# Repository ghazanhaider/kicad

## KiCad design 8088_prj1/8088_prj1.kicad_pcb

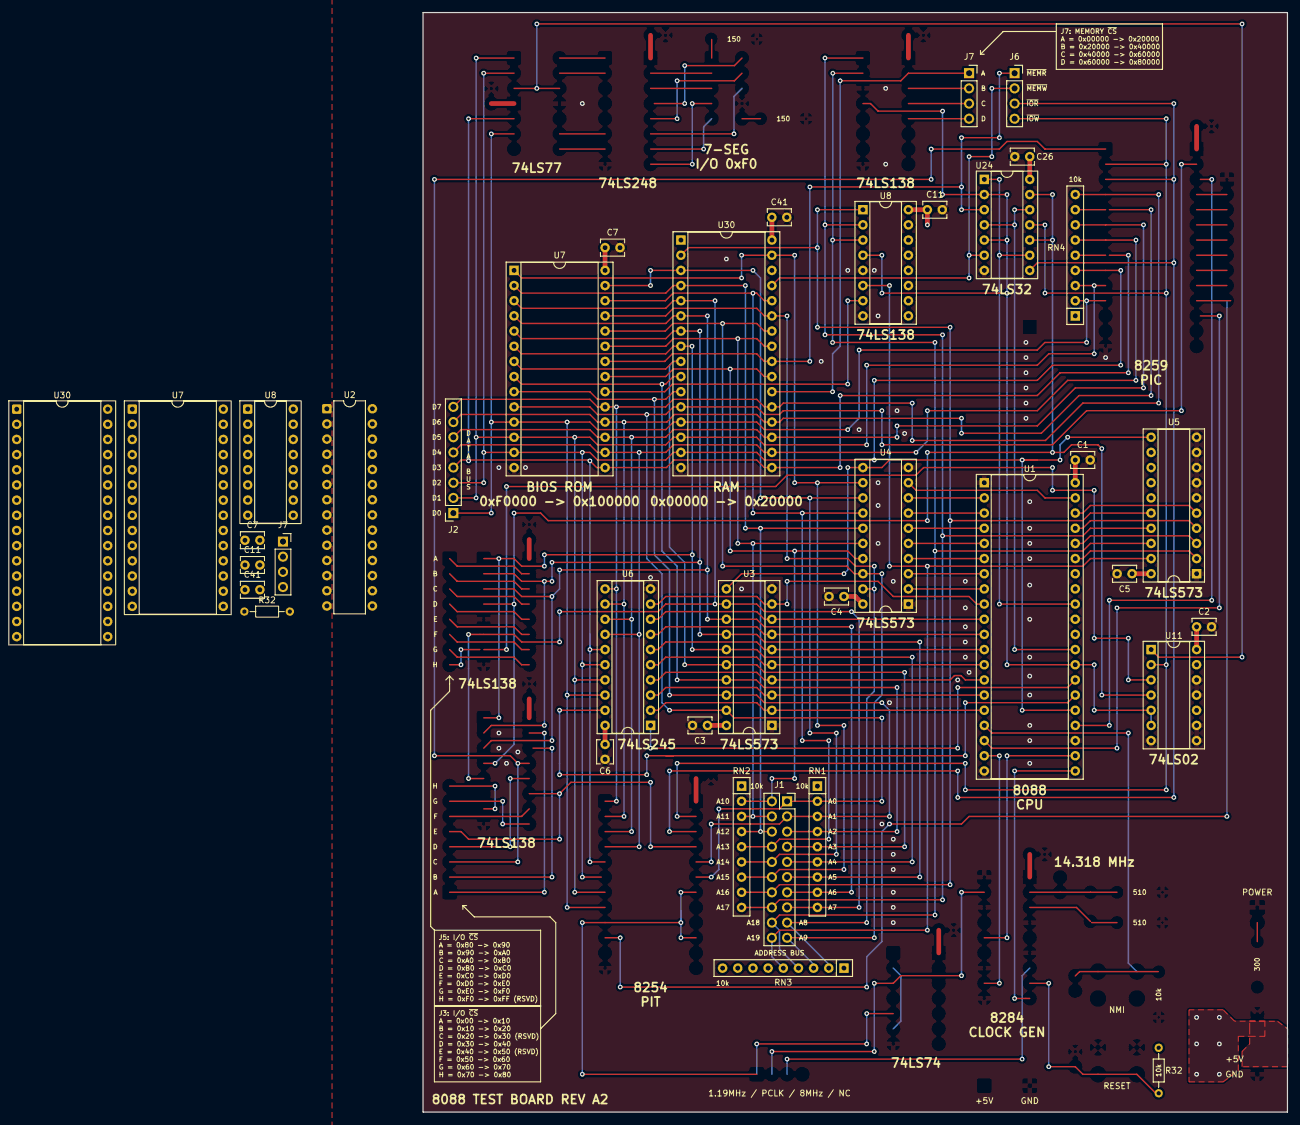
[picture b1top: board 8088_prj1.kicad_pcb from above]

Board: 4 copper layers, 144.8 x 184.1 mm, 38 parts (0 on the bottom side), 70 nets.

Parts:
C1, C2, C3, C4, C5, C6, C7, C7#2, C11, C11#2, C26, C41, C41#2: 0.1uF 20% Ceramic; C_Disc_D3.8mm_W2.6mm_P2.50mm
J1: Conn_02x10_Counter_Clockwise; PinSocket_2x10_P2.54mm_Vertical
J2: Conn_01x08; PinSocket_1x08_P2.54mm_Vertical
J6, J7, J7#2: Conn_01x04; PinSocket_1x04_P2.54mm_Vertical
R32, R32#2: 10k; R_Axial_DIN0204_L3.6mm_D1.6mm_P7.62mm_Horizontal
RN1, RN2, RN3, RN4: R_Network08; R_Array_SIP9
U1: 8088; DIP-40_W15.24mm_Socket
U2: ATmega328P-P; DIP-28_W7.62mm
U3, U4, U5: 74LS573; DIP-20_W7.62mm_Socket
U6: 74HC245; DIP-20_W7.62mm_Socket
U7: AT29F010B; DIP-28_W15.24mm_Socket
U7#2: W27C512 BIOS ROM; DIP-28_W15.24mm_Socket
U8, U8#2: 74LS138; DIP-16_W7.62mm_Socket
U11: 74LS02; DIP-14_W7.62mm_Socket
U24: 74LS32; DIP-14_W7.62mm_Socket
U30, U30#2: AS6C1008-55PCN; DIP-32_W15.24mm_Socket

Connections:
+5V: C1.1, C2.1, C3.1, C4.1, C5.1, C6.1, C7.1, C7#2.1, C11.1, C11#2.1, C26.1, C41.1, C41#2.1, R32.1, R32#2.1, RN1.1 (common), RN2.1 (common), RN3.1 (common), RN4.1 (common), U1.22 (READY), U1.33 (MN/~MX), U1.40 (VCC), U2.7 (VCC), U2.20 (AVCC), U3.20 (VCC), U4.20 (VCC), U5.20 (VCC), U6.20 (VCC), U7#2.28 (VCC), U8.6 (E3), U8.16 (VCC), U8#2.16 (VCC), U11.14 (VCC), U24.14 (VCC), U30.30 (CS2), U30.32 (VCC), U30#2.30 (CS2), U30#2.32 (VCC)
/8088_A8: U1.8 (A8), U4.2 (D0)
/8088_A9: U1.7 (A9), U4.3 (D1)
/8088_A10: U1.6 (A10), U4.4 (D2)
/8088_A11: U1.5 (A11), U4.5 (D3)
/8088_A12: U1.4 (A12), U4.6 (D4)
/8088_A13: U1.3 (A13), U4.7 (D5)
/8088_A14: U1.2 (A14), U4.8 (D6)
/8088_A15: U1.39 (A15), U4.9 (D7)
/8088_A16: U1.38 (A16/S3), U5.5 (D3)
/8088_A17: U1.37 (A17/S4), U5.4 (D2)
/8088_A18: U1.36 (A18/S5), U5.3 (D1)
/8088_A19: U1.35 (A19/S6), U5.2 (D0)
/8088_AD0: U1.16 (AD0), U3.2 (D0), U6.2 (A0)
/8088_AD1: U1.15 (AD1), U3.3 (D1), U6.3 (A1)
/8088_AD2: U1.14 (AD2), U3.4 (D2), U6.4 (A2)
/8088_AD3: U1.13 (AD3), U3.5 (D3), U6.5 (A3)
/8088_AD4: U1.12 (AD4), U3.6 (D4), U6.6 (A4)
/8088_AD5: U1.11 (AD5), U3.7 (D5), U6.7 (A5)
/8088_AD6: U1.10 (AD6), U3.8 (D6), U6.8 (A6)
/8088_AD7: U1.9 (AD7), U3.9 (D7), U6.9 (A7)
/8088_ALE: U1.25 (ALE), U3.11 (Load), U4.11 (Load), U5.11 (Load)
/8088_CLK: U1.19 (CLK), U2.15 (PB1)
/8088_DEN#: U1.26 (DEN), U6.19 (CE)
/8088_DT/R#: U1.27 (DT/~R), U6.1 (A->B)
/8088_IO/M#: U1.28 (IO/~M), U8.5 (E2), U8#2.4 (E1), U11.5, U11.6, U24.2, U24.5
/8088_RD#: U1.32 (~RD), U24.1, U24.9
/8088_RESET: R32#2.2, U1.21 (RESET), U2.10 (XTAL2/PB7)
/8088_WR#: U1.29 (WR), U24.4, U24.12
/A0: J1.1, RN1.2 (R1), U3.19 (Q0), U7.12 (A0), U7#2.10 (A0), U30.12 (A0), U30#2.12 (A0)
/A1: J1.3, RN1.3 (R2), U3.18 (Q1), U7.11 (A1), U7#2.9 (A1), U30.11 (A1), U30#2.11 (A1)
/A2: J1.5, RN1.4 (R3), U3.17 (Q2), U7.10 (A2), U7#2.8 (A2), U30.10 (A2), U30#2.10 (A2)
/A3: J1.7, RN1.5 (R4), U3.16 (Q3), U7.9 (A3), U7#2.7 (A3), U30.9 (A3), U30#2.9 (A3)
/A4: J1.9, RN1.6 (R5), U3.15 (Q4), U7.8 (A4), U7#2.6 (A4), U30.8 (A4), U30#2.8 (A4)
/A5: J1.11, RN1.7 (R6), U3.14 (Q5), U7.7 (A5), U7#2.5 (A5), U30.7 (A5), U30#2.7 (A5)
/A6: J1.13, RN1.8 (R7), U3.13 (Q6), U7.6 (A6), U7#2.4 (A6), U30.6 (A6), U30#2.6 (A6)
/A7: J1.15, RN1.9 (R8), U3.12 (Q7), U7.5 (A7), U7#2.3 (A7), U30.5 (A7), U30#2.5 (A7)
/A8: J1.17, RN3.2 (R1), U4.19 (Q0), U7.27 (A8), U7#2.25 (A8), U30.27 (A8), U30#2.27 (A8)
/A9: J1.19, RN3.3 (R2), U4.18 (Q1), U7.26 (A9), U7#2.24 (A9), U30.26 (A9), U30#2.26 (A9)
/A10: J1.2, RN2.2 (R1), U4.17 (Q2), U7.23 (A10), U7#2.21 (A10), U30.23 (A10), U30#2.23 (A10)
/A11: J1.4, RN2.3 (R2), U4.16 (Q3), U7.25 (A11), U7#2.23 (A11), U30.25 (A11), U30#2.25 (A11)
/A12: J1.6, RN2.4 (R3), U4.15 (Q4), U7.4 (A12), U7#2.2 (A12), U30.4 (A12), U30#2.4 (A12)
/A13: J1.8, RN2.5 (R4), U4.14 (Q5), U7.28 (A13), U7#2.26 (A13), U30.28 (A13), U30#2.28 (A13)
/A14: J1.10, RN2.6 (R5), U4.13 (Q6), U7#2.27 (A14), U30.3 (A14), U30#2.3 (A14)
/A15: J1.12, RN2.7 (R6), U4.12 (Q7), U7.3 (A15), U7#2.1 (A15), U30.31 (A15)
/A16: J1.14, RN2.8 (R7), U5.16 (Q3), U7.2 (A16), U8#2.1 (A0), U30.2 (A16)
/A17: J1.16, RN2.9 (R8), U5.17 (Q2), U8.1 (A0), U8#2.2 (A1)
/A18: J1.18, RN3.4 (R3), U5.18 (Q1), U8.2 (A1), U8#2.3 (A2)
/A19: J1.20, RN3.5 (R4), U5.19 (Q0), U8.3 (A2), U8#2.6 (E3)
/BIOS_ROM_CS#: U7.22 (CE), U7#2.20 (CE#), U8.7 (O7), U8#2.7 (O7)
/D0: J2.1, RN4.2 (R1), U6.18 (B0), U7.13 (D0), U7#2.11 (Q0), U30.13 (Q0), U30#2.13 (Q0)
/D1: J2.2, RN4.3 (R2), U6.17 (B1), U7.14 (D1), U7#2.12 (Q1), U30.14 (Q1), U30#2.14 (Q1)
/D2: J2.3, RN4.4 (R3), U6.16 (B2), U7.15 (D2), U7#2.13 (Q2), U30.15 (Q2), U30#2.15 (Q2)
/D3: J2.4, RN4.5 (R4), U6.15 (B3), U7.17 (D3), U7#2.15 (Q3), U30.17 (Q3), U30#2.17 (Q3)
/D4: J2.5, RN4.6 (R5), U6.14 (B4), U7.18 (D4), U7#2.16 (Q4), U30.18 (Q4), U30#2.18 (Q4)
/D5: J2.6, RN4.7 (R6), U6.13 (B5), U7.19 (D5), U7#2.17 (Q5), U30.19 (Q5), U30#2.19 (Q5)
/D6: J2.7, RN4.8 (R7), U6.12 (B6), U7.20 (D6), U7#2.18 (Q6), U30.20 (Q6), U30#2.20 (Q6)
/D7: J2.8, RN4.9 (R8), U6.11 (B7), U7.21 (D7), U7#2.19 (Q7), U30.21 (Q7), U30#2.21 (Q7)
/RAM/~RAM_A_CS: J7.1, U30.22 (~CS1)
/RAM_CS#: U8.15 (O0), U30#2.22 (~CS1)
/~IOR: J6.3, U24.8
/~IOW: J6.4, U24.11
/~MEMR: J6.1, U7.24 (OE), U7#2.22 (OE#), U24.3, U30.24 (~OE), U30#2.24 (~OE)
/~MEMW: J6.2, U24.6, U30.29 (~WE), U30#2.29 (~WE)
GND: C1.2, C2.2, C3.2, C4.2, C5.2, C6.2, C7.2, C7#2.2, C11.2, C11#2.2, C26.2, C41.2, C41#2.2, U1.1 (GND), U1.17 (NMI), U1.18 (INTR), U1.20 (GND), U1.23 (~TEST), U1.31 (HOLD), U2.8 (GND), U2.22 (GND), U3.1 (OE), U3.10 (GND), U4.1 (OE), U4.10 (GND), U5.1 (OE), U5.6 (D4), U5.7 (D5), U5.8 (D6), U5.9 (D7), U5.10 (GND), U6.10 (GND), U7.16 (GND), U7#2.14 (GND), U8.4 (E1), U8.8 (GND), U8#2.5 (E2), U8#2.8 (GND), U11.2, U11.3, U11.7 (GND), U11.8, U11.9, U11.11, U11.12, U24.7 (GND), U30.16 (GND), U30#2.16 (GND)
unnamed: J7#2.1, U8.14 (O1)
unnamed: J7.2, J7#2.2, U8.13 (O2)
unnamed: J7.3, J7#2.3, U8.12 (O3)
unnamed: J7.4, J7#2.4, U8.11 (O4)
unnamed: U11.4, U24.10, U24.13

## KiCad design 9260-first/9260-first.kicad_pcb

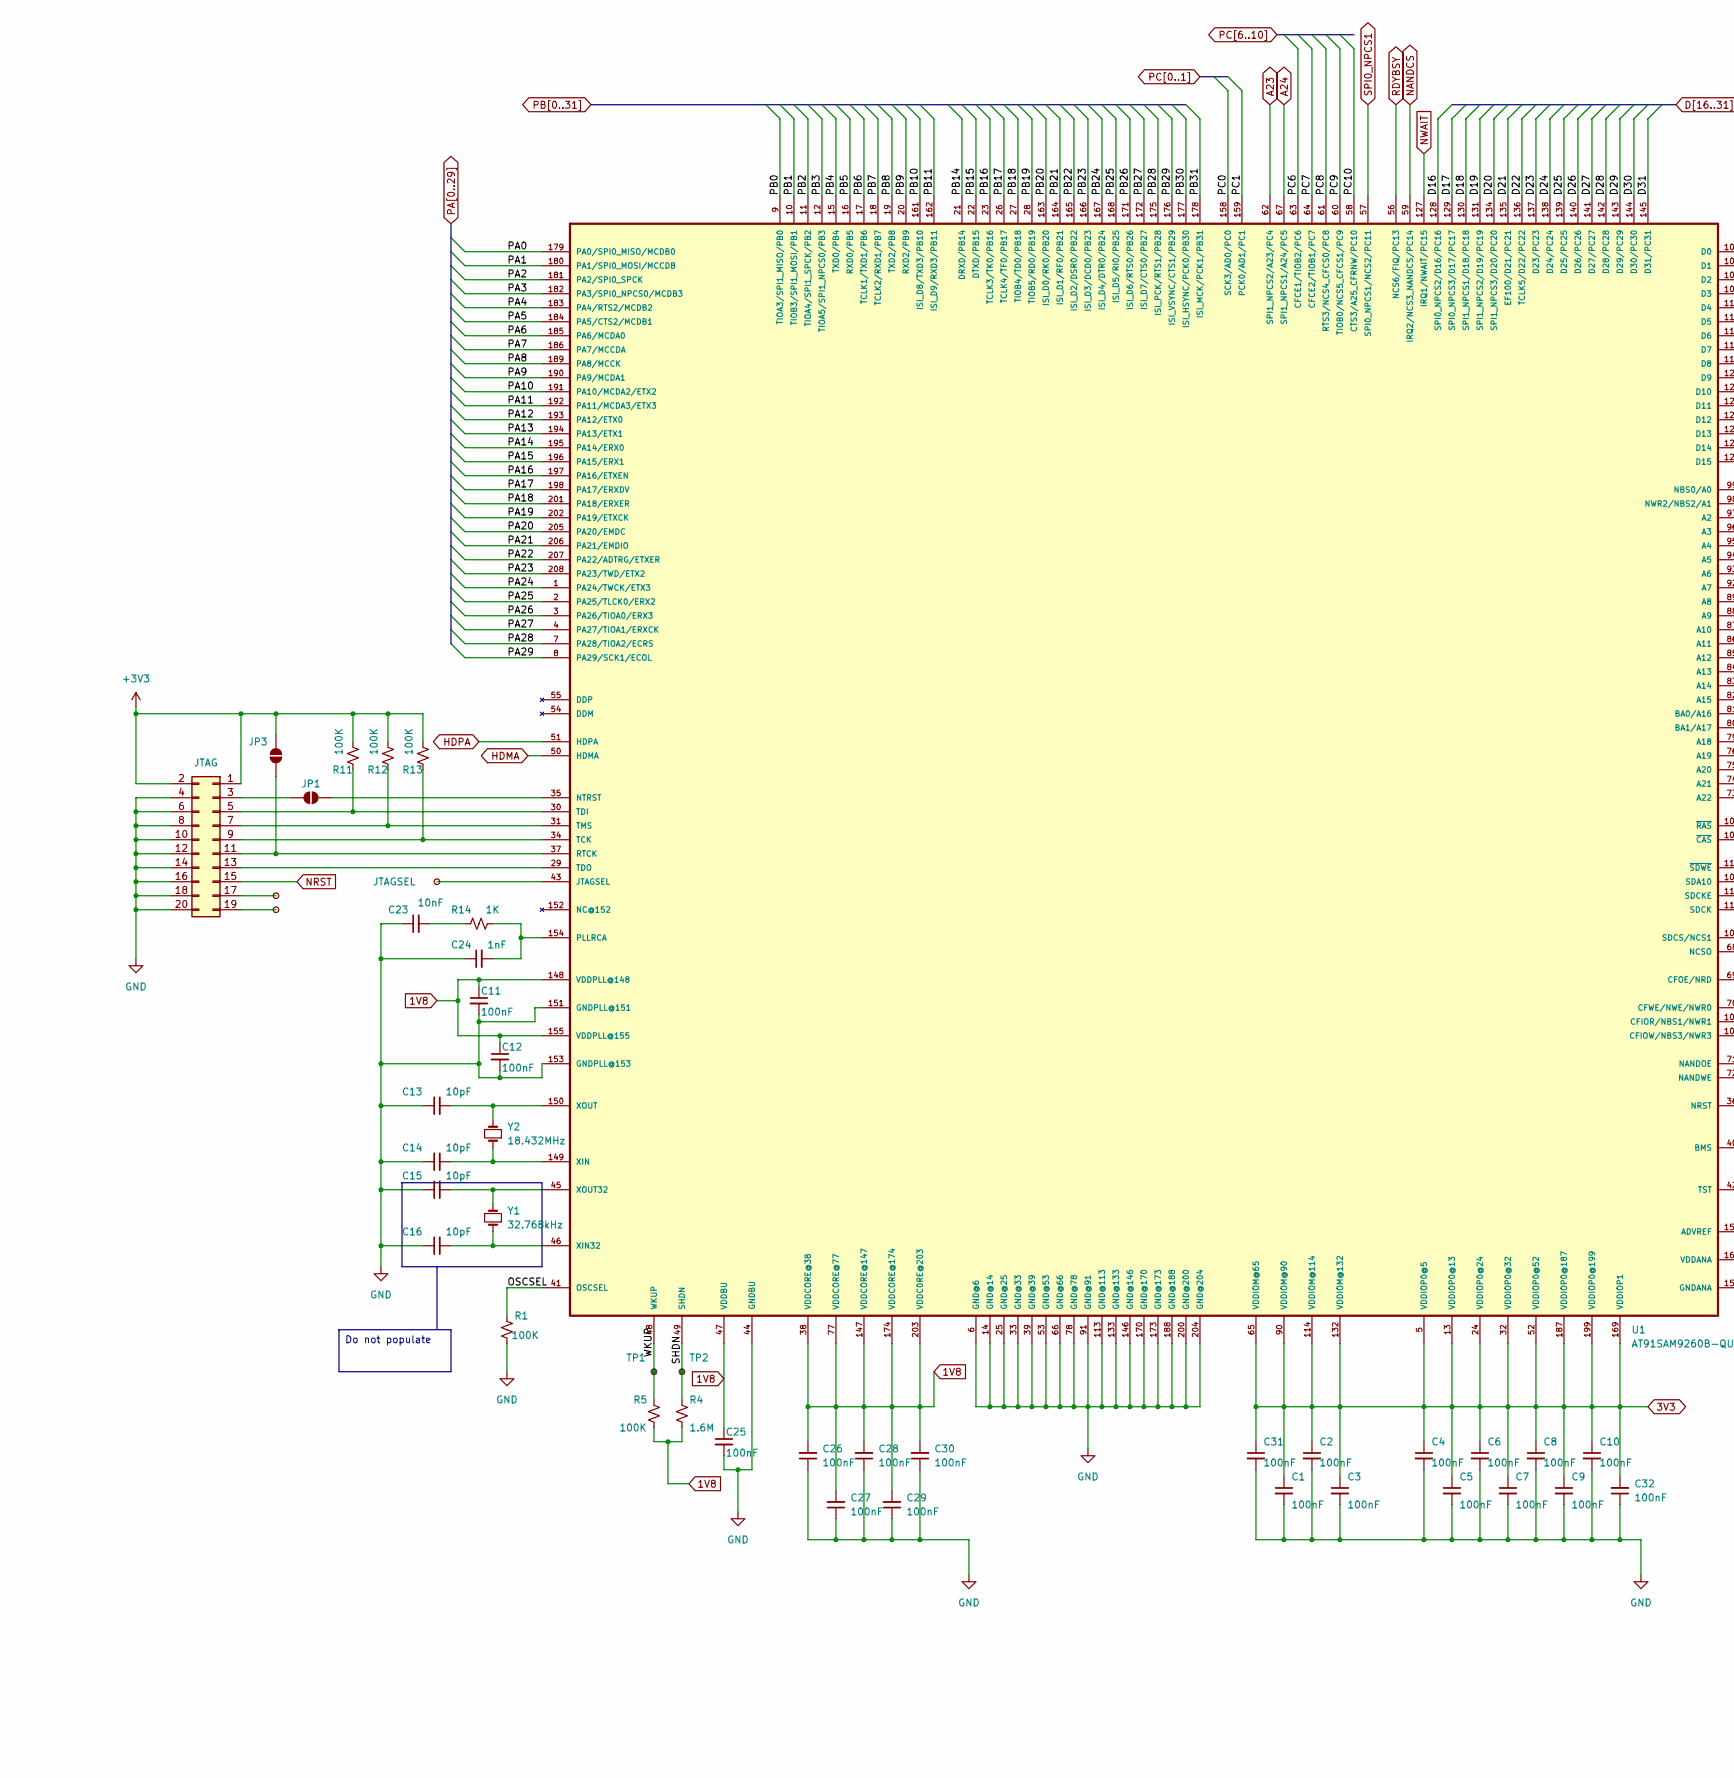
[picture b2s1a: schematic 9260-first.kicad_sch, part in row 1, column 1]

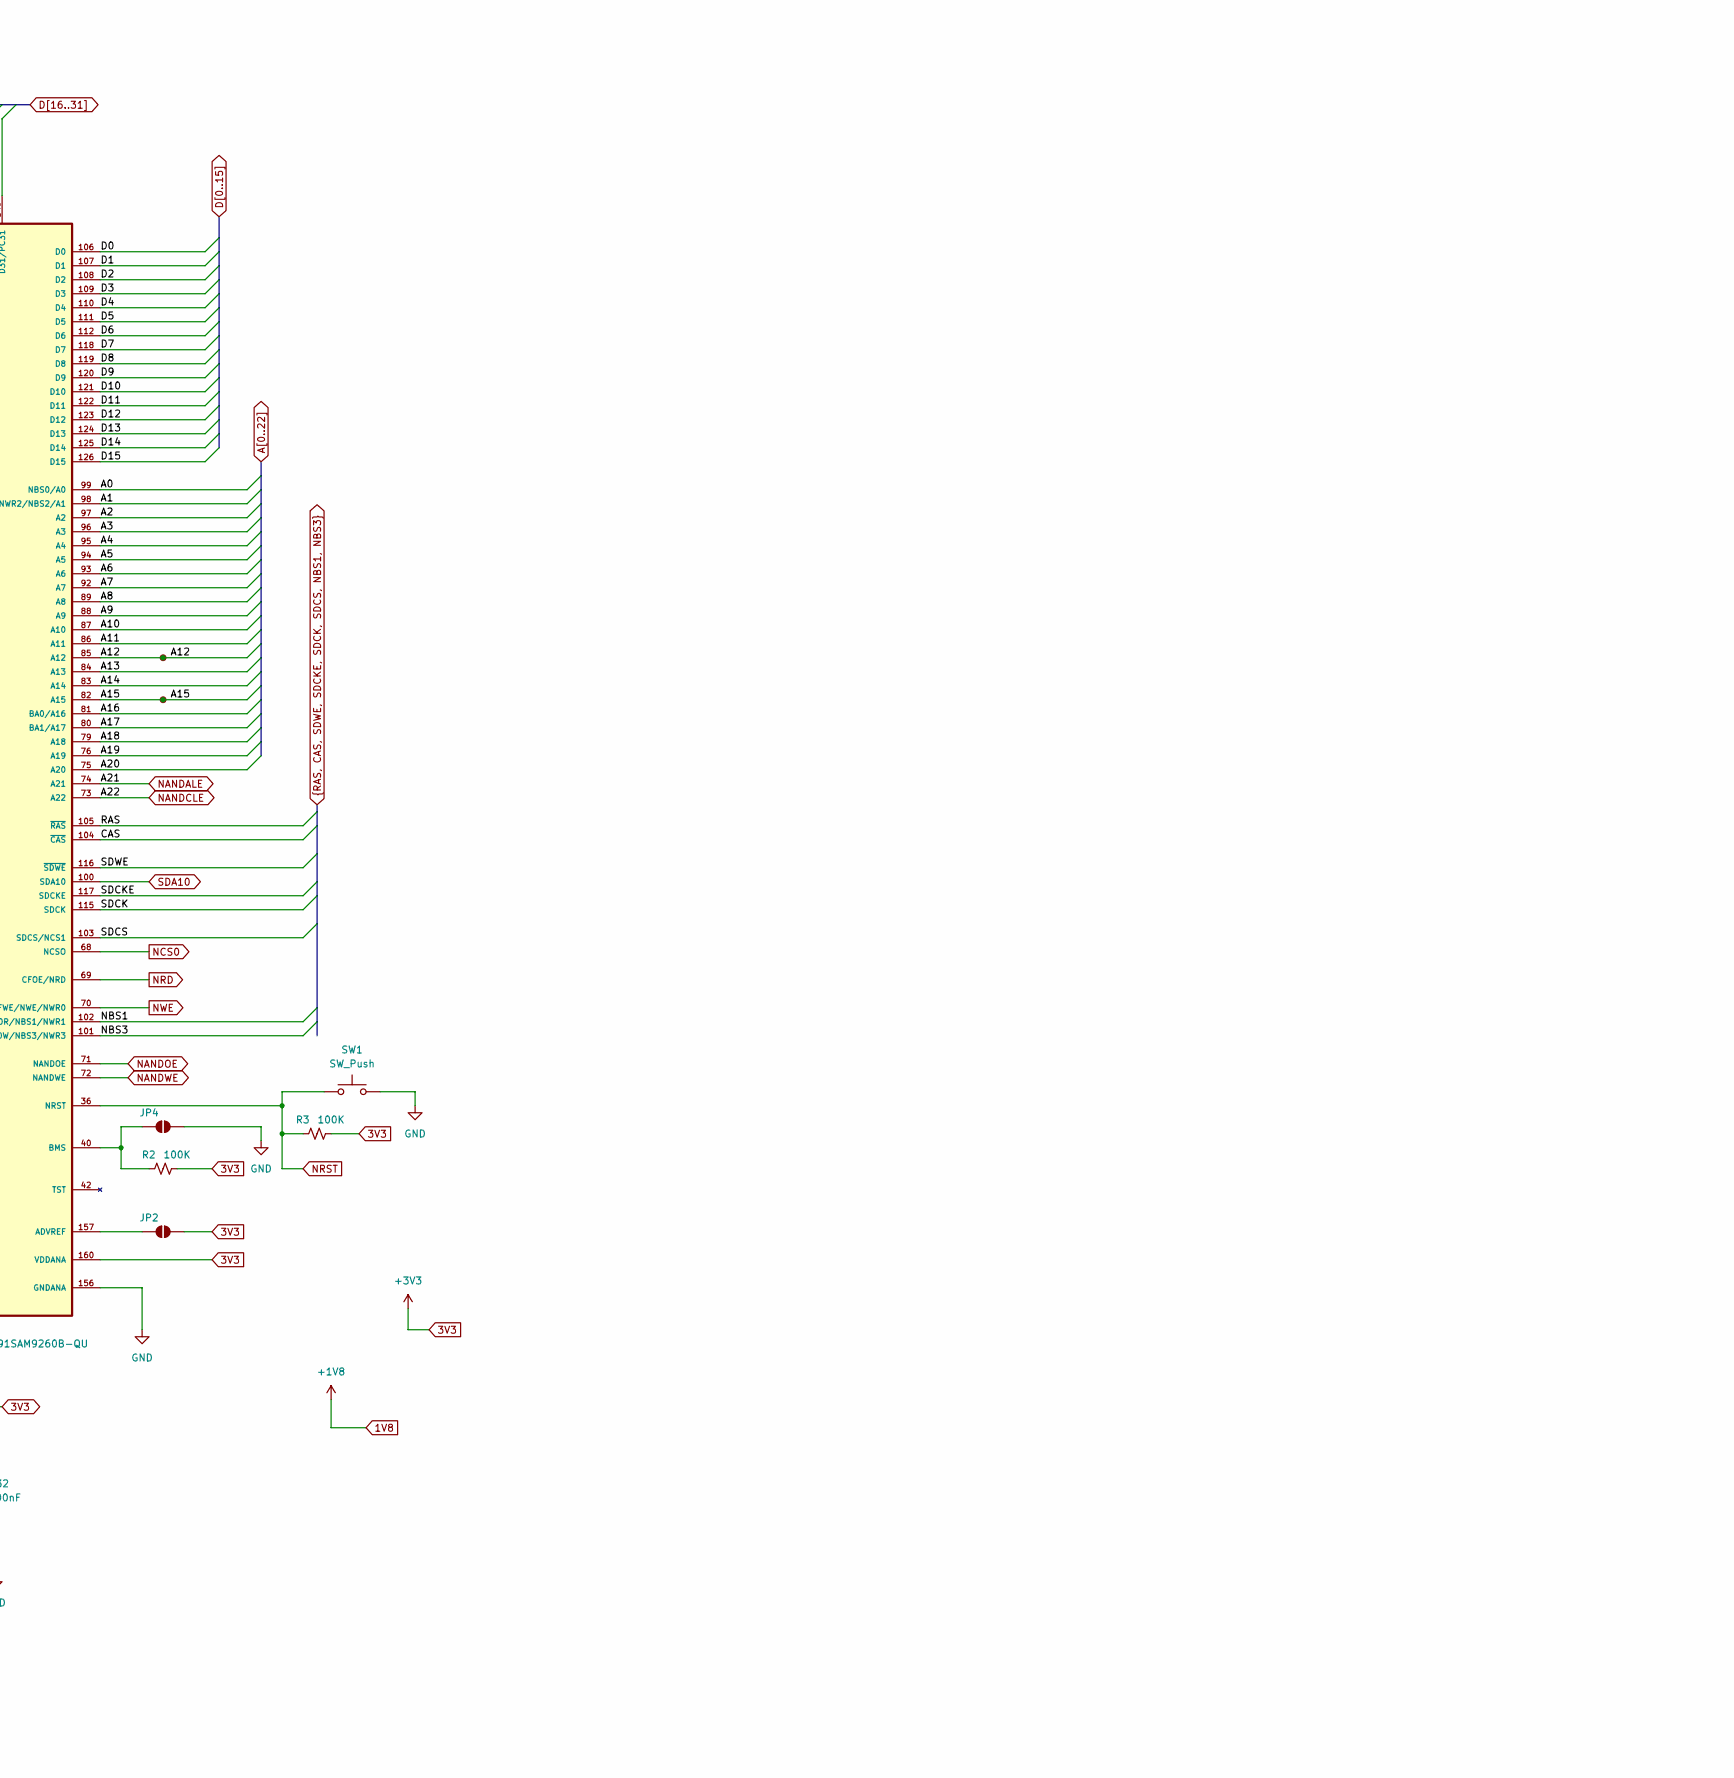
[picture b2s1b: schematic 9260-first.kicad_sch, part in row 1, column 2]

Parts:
C1, C2, C3, C4, C5, C6, C7, C8, C9, C10, C11, C12, C25, C26, C27, C28, C29, C30, C31, C32: 100nF; C_0805_2012Metric
C13, C14, C15, C16: 10pF; C_0805_2012Metric
C23: 10nF; C_0805_2012Metric
C24: 1nF; C_0805_2012Metric
J1: JTAG; PinHeader_2x10_P2.54mm_Vertical
JP1, JP2, JP3, JP4: SolderJumper_2_Open; SolderJumper-2_P1.3mm_Open_Pad1.0x1.5mm
R1, R2, R3, R5, R11, R12, R13: 100K; R_0805_2012Metric
R4: 1.6M; R_0805_2012Metric
R14: 1K; R_0805_2012Metric
SW1: SW_Push; SW_Push_1P1T_NO_6x6mm_H9.5mm
TP1, TP2: TestPoint_Small; TestPoint_Plated_Hole_D2.0mm
TP3, TP5, TP7: A12; TestPoint_Plated_Hole_D2.0mm
TP4: A15; TestPoint_Plated_Hole_D2.0mm
TP6: JTAGSEL; TestPoint_Plated_Hole_D2.0mm
U1: AT91SAM9260B-QU; PQFP208
Y1: 32.768kHz; Crystal_SMD_HC49-SD
Y2: 18.432MHz; Crystal_SMD_HC49-SD

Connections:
1V8: C11.1, C12.1, C25.1, C26.2, C27.2, C28.2, C29.2, C30.2, R4.2, R5.2, U1.38 (VDDCORE@38), U1.47 (VDDBU), U1.77 (VDDCORE@77), U1.147 (VDDCORE@147), U1.148 (VDDPLL@148), U1.155 (VDDPLL@155), U1.174 (VDDCORE@174), U1.203 (VDDC0RE@203); also elsewhere on the board
3V3: C1.1, C2.1, C3.1, C4.1, C5.1, C6.1, C7.1, C8.1, C9.1, C10.1, C31.1, C32.2, J1.1, J1.2, JP2.2 (B), JP3.2 (B), R2.2, R3.2, R11.1, R12.1, R13.1, U1.5 (VDDIOP0@5), U1.13 (VDDIOP0@13), U1.24 (VDDIOP0@24), U1.32 (VDDIOP0@32), U1.52 (VDDIOP0@52), U1.65 (VDDIOM@65), U1.90 (VDDIOM@90), U1.114 (VDDIOM@114), U1.132 (VDDIOM@132), U1.160 (VDDANA), U1.169 (VDDIOP1), U1.187 (VDDIOP0@187), U1.199 (VDDIOP0@199); also elsewhere on the board
/OSCSEL: R1.1, U1.41 (OSCSEL)
/SHDN: R4.1, TP2.1, U1.49 (SHDN)
/WKUP: R5.1, TP1.1, U1.48 (WKUP)
A0: U1.99 (NBS0/A0); also elsewhere on the board
A1: U1.98 (NWR2/NBS2/A1); also elsewhere on the board
A2: U1.97 (A2); also elsewhere on the board
A3: U1.96 (A3); also elsewhere on the board
A4: U1.95 (A4); also elsewhere on the board
A5: U1.94 (A5); also elsewhere on the board
A6: U1.93 (A6); also elsewhere on the board
A7: U1.92 (A7); also elsewhere on the board
A8: U1.89 (A8); also elsewhere on the board
A9: U1.88 (A9); also elsewhere on the board
A10: U1.87 (A10); also elsewhere on the board
A11: U1.86 (A11); also elsewhere on the board
A12: TP3.1, U1.85 (A12)
A13: U1.84 (A13); also elsewhere on the board
A14: U1.83 (A14); also elsewhere on the board
A15: TP4.1, U1.82 (A15)
A16: U1.81 (BA0/A16); also elsewhere on the board
A17: U1.80 (BA1/A17); also elsewhere on the board
A18: U1.79 (A18)
A19: U1.76 (A19)
A20: U1.75 (A20)
A23: U1.62 (SPI1_NPCS2/A23/PC4)
A24: U1.67 (SPI1_NPCS1/A24/PC5)
CAS: U1.104 (~CAS); also elsewhere on the board
D0: U1.106 (D0); also elsewhere on the board
D1: U1.107 (D1); also elsewhere on the board
D2: U1.108 (D2); also elsewhere on the board
D3: U1.109 (D3); also elsewhere on the board
D4: U1.110 (D4); also elsewhere on the board
D5: U1.111 (D5); also elsewhere on the board
D6: U1.112 (D6); also elsewhere on the board
D7: U1.118 (D7); also elsewhere on the board
D8: U1.119 (D8); also elsewhere on the board
D9: U1.120 (D9); also elsewhere on the board
D10: U1.121 (D10); also elsewhere on the board
D11: U1.122 (D11); also elsewhere on the board
D12: U1.123 (D12); also elsewhere on the board
D13: U1.124 (D13); also elsewhere on the board
D14: U1.125 (D14); also elsewhere on the board
D15: U1.126 (D15); also elsewhere on the board
D16: U1.128 (SPI0_NPCS2/D16/PC16); also elsewhere on the board
D17: U1.129 (SPI0_NPCS3/D17/PC17); also elsewhere on the board
D18: U1.130 (SPI1_NPCS1/D18/PC18); also elsewhere on the board
D19: U1.131 (SPI1_NPCS2/D19/PC19); also elsewhere on the board
D20: U1.134 (SPI1_NPCS3/D20/PC20); also elsewhere on the board
D21: U1.135 (EF100/D21/PC21); also elsewhere on the board
D22: U1.136 (TCLK5/D22/PC22); also elsewhere on the board
D23: U1.137 (D23/PC23); also elsewhere on the board
D24: U1.138 (D24/PC24); also elsewhere on the board
D25: U1.139 (D25/PC25); also elsewhere on the board
D26: U1.140 (D26/PC26); also elsewhere on the board
D27: U1.141 (D27/PC27); also elsewhere on the board
D28: U1.142 (D28/PC28); also elsewhere on the board
D29: U1.143 (D29/PC29); also elsewhere on the board
D30: U1.144 (D30/PC30); also elsewhere on the board
D31: U1.145 (D31/PC31); also elsewhere on the board
GND: C1.2, C2.2, C3.2, C4.2, C5.2, C6.2, C7.2, C8.2, C9.2, C10.2, C11.2, C12.2, C13.1, C14.1, C15.1, C16.1, C23.1, C24.1, C25.2, C26.1, C27.1, C28.1, C29.1, C30.1, C31.2, C32.1, J1.4, J1.6, J1.8, J1.10, J1.12, J1.14, J1.16, J1.18, J1.20, JP4.2 (B), R1.2, SW1.2, U1.6 (GND@6), U1.14 (GND@14), U1.25 (GND@25), U1.33 (GND@33), U1.39 (GND@39), U1.44 (GNDBU), U1.53 (GND@53), U1.66 (GND@66), U1.78 (GND@78), U1.91 (GND@91), U1.113 (GND@113), U1.133 (GND@133), U1.146 (GND@146), U1.151 (GNDPLL@151), U1.153 (GNDPLL@153), U1.156 (GNDANA), U1.170 (GND@170), U1.173 (GND@173), U1.188 (GND@188), U1.200 (GND@200), U1.204 (GND@204); also elsewhere on the board
HDMA: U1.50 (HDMA); also elsewhere on the board
HDPA: U1.51 (HDPA); also elsewhere on the board
NANDALE: U1.74 (A21)
NANDCLE: U1.73 (A22)
NANDCS: U1.59 (IRQ2/NCS3_NANDCS/PC14)
NANDOE: U1.71 (NANDOE)
NANDWE: U1.72 (NANDWE)
NBS1: U1.102 (CFIOR/NBS1/NWR1); also elsewhere on the board
NBS3: U1.101 (CFIOW/NBS3/NWR3); also elsewhere on the board
NCS0: U1.68 (NCSO)
NRD: U1.69 (CFOE/NRD)
NRST: J1.15, R3.1, SW1.1, U1.36 (NRST); also elsewhere on the board
NWAIT: U1.127 (IRQ1/NWAIT/PC15)
NWE: U1.70 (CFWE/NWE/NWR0)
unnamed: C23.2, R14.1
unnamed: J1.3, JP1.1 (A)
unnamed: J1.5, R11.2, U1.30 (TDI)
unnamed: J1.7, R12.2, U1.31 (TMS)
unnamed: J1.9, R13.2, U1.34 (TCK)
unnamed: J1.11, JP3.1 (A), U1.37 (RTCK)
unnamed: J1.13, U1.29 (TDO)
unnamed: J1.17, TP5.1
unnamed: J1.19, TP7.1
unnamed: JP1.2 (B), U1.35 (NTRST)
unnamed: JP2.1 (A), U1.157 (ADVREF)
unnamed: JP4.1 (A), R2.1, U1.40 (BMS)
unnamed: TP6.1, U1.43 (JTAGSEL)
unnamed: C24.2, R14.2, U1.154 (PLLRCA)
unnamed: C16.2, U1.46 (XIN32), Y1.1
unnamed: C14.2, U1.149 (XIN), Y2.1
unnamed: C15.2, U1.45 (XOUT32), Y1.2
unnamed: C13.2, U1.150 (XOUT), Y2.2
PA0: U1.179 (PA0/SPI0_MISO/MCDB0); also elsewhere on the board
PA1: U1.180 (PA1/SPI0_MOSI/MCCDB); also elsewhere on the board
PA2: U1.181 (PA2/SPI0_SPCK); also elsewhere on the board
PA3: U1.182 (PA3/SPI0_NPCS0/MCDB3); also elsewhere on the board
PA4: U1.183 (PA4/RTS2/MCDB2); also elsewhere on the board
PA5: U1.184 (PA5/CTS2/MCDB1); also elsewhere on the board
PA6: U1.185 (PA6/MCDA0); also elsewhere on the board
PA7: U1.186 (PA7/MCCDA); also elsewhere on the board
PA8: U1.189 (PA8/MCCK); also elsewhere on the board
PA9: U1.190 (PA9/MCDA1); also elsewhere on the board
PA10: U1.191 (PA10/MCDA2/ETX2); also elsewhere on the board
PA11: U1.192 (PA11/MCDA3/ETX3); also elsewhere on the board
PA12: U1.193 (PA12/ETX0); also elsewhere on the board
PA13: U1.194 (PA13/ETX1); also elsewhere on the board
PA14: U1.195 (PA14/ERX0); also elsewhere on the board
PA15: U1.196 (PA15/ERX1); also elsewhere on the board
PA16: U1.197 (PA16/ETXEN); also elsewhere on the board
PA17: U1.198 (PA17/ERXDV); also elsewhere on the board
PA18: U1.201 (PA18/ERXER); also elsewhere on the board
PA19: U1.202 (PA19/ETXCK); also elsewhere on the board
PA20: U1.205 (PA20/EMDC); also elsewhere on the board
PA21: U1.206 (PA21/EMDIO); also elsewhere on the board
PA22: U1.207 (PA22/ADTRG/ETXER); also elsewhere on the board
PA23: U1.208 (PA23/TWD/ETX2); also elsewhere on the board
PA24: U1.1 (PA24/TWCK/ETX3); also elsewhere on the board
PA25: U1.2 (PA25/TLCK0/ERX2); also elsewhere on the board
PA26: U1.3 (PA26/TIOA0/ERX3); also elsewhere on the board
PA27: U1.4 (PA27/TIOA1/ERXCK); also elsewhere on the board
PA28: U1.7 (PA28/TIOA2/ECRS); also elsewhere on the board
PA29: U1.8 (PA29/SCK1/ECOL); also elsewhere on the board
PB0: U1.9 (TIOA3/SPI1_MISO/PB0)
PB1: U1.10 (TIOB3/SPI1_MOSI/PB1)
PB2: U1.11 (TIOA4/SPI1_SPCK/PB2)
PB3: U1.12 (TIOA5/SPI1_NPCS0/PB3)
PB4: U1.15 (TXD0/PB4)
PB5: U1.16 (RXD0/PB5)
PB6: U1.17 (TCLK1/TXD1/PB6)
PB7: U1.18 (TCLK2/RXD1/PB7)
PB8: U1.19 (TXD2/PB8)
PB9: U1.20 (RXD2/PB9)
PB10: U1.161 (ISI_D8/TXD3/PB10); also elsewhere on the board
PB11: U1.162 (ISI_D9/RXD3/PB11); also elsewhere on the board
PB14: U1.21 (DRXD/PB14); also elsewhere on the board
PB15: U1.22 (DTXD/PB15); also elsewhere on the board
PB16: U1.23 (TCLK3/TK0/PB16)
PB17: U1.26 (TCLK4/TF0/PB17)
PB18: U1.27 (TIOB4/TD0/PB18)
PB19: U1.28 (TIOB5/RD0/PB19)
PB20: U1.163 (ISI_D0/RK0/PB20); also elsewhere on the board
PB21: U1.164 (ISI_D1/RF0/PB21); also elsewhere on the board
PB22: U1.165 (ISI_D2/DSR0/PB22); also elsewhere on the board
PB23: U1.166 (ISI_D3/DCD0/PB23); also elsewhere on the board
PB24: U1.167 (ISI_D4/DTR0/PB24); also elsewhere on the board
PB25: U1.168 (ISI_D5/RI0/PB25); also elsewhere on the board
PB26: U1.171 (ISI_D6/RTS0/PB26); also elsewhere on the board
PB27: U1.172 (ISI_D7/CTS0/PB27); also elsewhere on the board
PB28: U1.175 (ISI_PCK/RTS1/PB28); also elsewhere on the board
PB29: U1.176 (ISI_VSYNC/CTS1/PB29); also elsewhere on the board
PB30: U1.177 (ISI_HSYNC/PCK0/PB30); also elsewhere on the board
PB31: U1.178 (ISI_MCK/PCK1/PB31); also elsewhere on the board
PC0: U1.158 (SCK3/AD0/PC0); also elsewhere on the board
PC1: U1.159 (PCK0/AD1/PC1); also elsewhere on the board
PC6: U1.63 (CFCE1/TIOB2/PC6)
PC7: U1.64 (CFCE2/TIOB1/PC7)
PC8: U1.61 (RTS3/NCS4_CFCS0/PC8)
PC9: U1.60 (TIOB0/NCS5_CFCS1/PC9)
PC10: U1.58 (CTS3/A25_CFRNW/PC10)
RAS: U1.105 (~RAS); also elsewhere on the board
RDYBSY: U1.56 (NCS6/FIQ/PC13)
SDA10: U1.100 (SDA10); also elsewhere on the board
SDCK: U1.115 (SDCK); also elsewhere on the board
SDCKE: U1.117 (SDCKE); also elsewhere on the board
SDCS: U1.103 (SDCS/NCS1); also elsewhere on the board
SDWE: U1.116 (~SDWE); also elsewhere on the board
SPI0_NPCS1: U1.57 (SPI0_NPCS1/NCS2/PC11); also elsewhere on the board

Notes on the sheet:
Do not populate

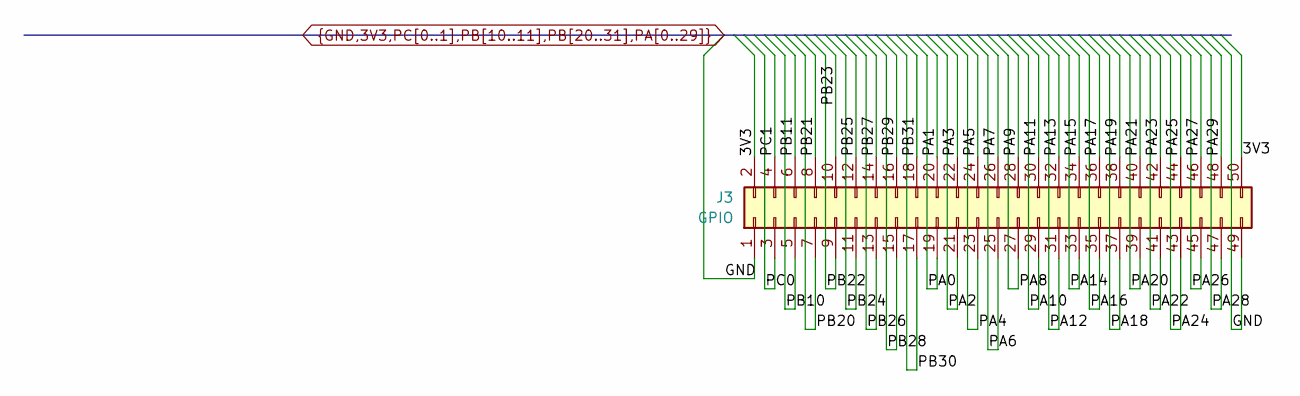
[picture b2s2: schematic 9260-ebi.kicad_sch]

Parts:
J3: GPIO; PinHeader_2x25_P2.54mm_Vertical

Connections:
3V3: J3.2, J3.50; also elsewhere on the board
GND: J3.1, J3.49; also elsewhere on the board
PA0: J3.19; also elsewhere on the board
PA1: J3.20; also elsewhere on the board
PA2: J3.21; also elsewhere on the board
PA3: J3.22; also elsewhere on the board
PA4: J3.23; also elsewhere on the board
PA5: J3.24; also elsewhere on the board
PA6: J3.25; also elsewhere on the board
PA7: J3.26; also elsewhere on the board
PA8: J3.27; also elsewhere on the board
PA9: J3.28; also elsewhere on the board
PA10: J3.29; also elsewhere on the board
PA11: J3.30; also elsewhere on the board
PA12: J3.31; also elsewhere on the board
PA13: J3.32; also elsewhere on the board
PA14: J3.33; also elsewhere on the board
PA15: J3.34; also elsewhere on the board
PA16: J3.35; also elsewhere on the board
PA17: J3.36; also elsewhere on the board
PA18: J3.37; also elsewhere on the board
PA19: J3.38; also elsewhere on the board
PA20: J3.39; also elsewhere on the board
PA21: J3.40; also elsewhere on the board
PA22: J3.41; also elsewhere on the board
PA23: J3.42; also elsewhere on the board
PA24: J3.43; also elsewhere on the board
PA25: J3.44; also elsewhere on the board
PA26: J3.45; also elsewhere on the board
PA27: J3.46; also elsewhere on the board
PA28: J3.47; also elsewhere on the board
PA29: J3.48; also elsewhere on the board
PB10: J3.5; also elsewhere on the board
PB11: J3.6; also elsewhere on the board
PB20: J3.7; also elsewhere on the board
PB21: J3.8; also elsewhere on the board
PB22: J3.9; also elsewhere on the board
PB23: J3.10; also elsewhere on the board
PB24: J3.11; also elsewhere on the board
PB25: J3.12; also elsewhere on the board
PB26: J3.13; also elsewhere on the board
PB27: J3.14; also elsewhere on the board
PB28: J3.15; also elsewhere on the board
PB29: J3.16; also elsewhere on the board
PB30: J3.17; also elsewhere on the board
PB31: J3.18; also elsewhere on the board
PC0: J3.3; also elsewhere on the board
PC1: J3.4; also elsewhere on the board

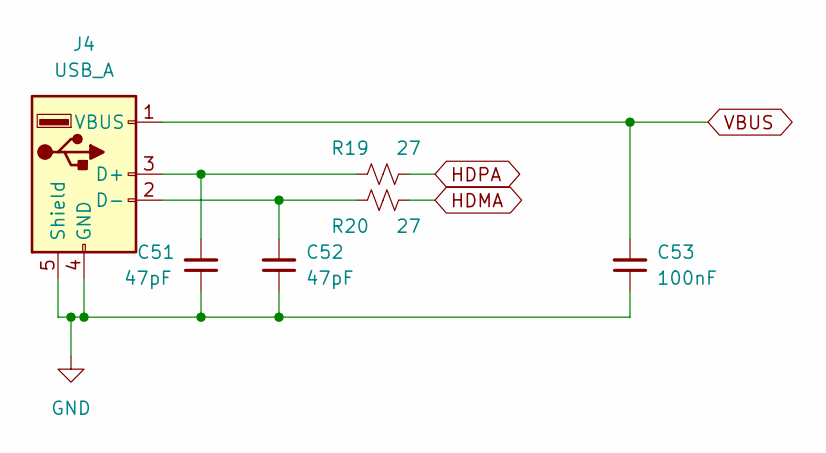
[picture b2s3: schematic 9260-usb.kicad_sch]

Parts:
C51, C52: 47pF; C_0805_2012Metric
C53: 100nF; C_0805_2012Metric
J4: USB_A; USB_A_Receptacle_GCT_USB1046
R19, R20: 27; R_0805_2012Metric

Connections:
GND: C51.1, C52.1, C53.1, J4.4 (GND), J4.5 (Shield); also elsewhere on the board
HDMA: R20.2; also elsewhere on the board
HDPA: R19.2; also elsewhere on the board
unnamed: C51.2, J4.3 (D+), R19.1
unnamed: C52.2, J4.2 (D-), R20.1
VBUS: C53.2, J4.1 (VBUS); also elsewhere on the board

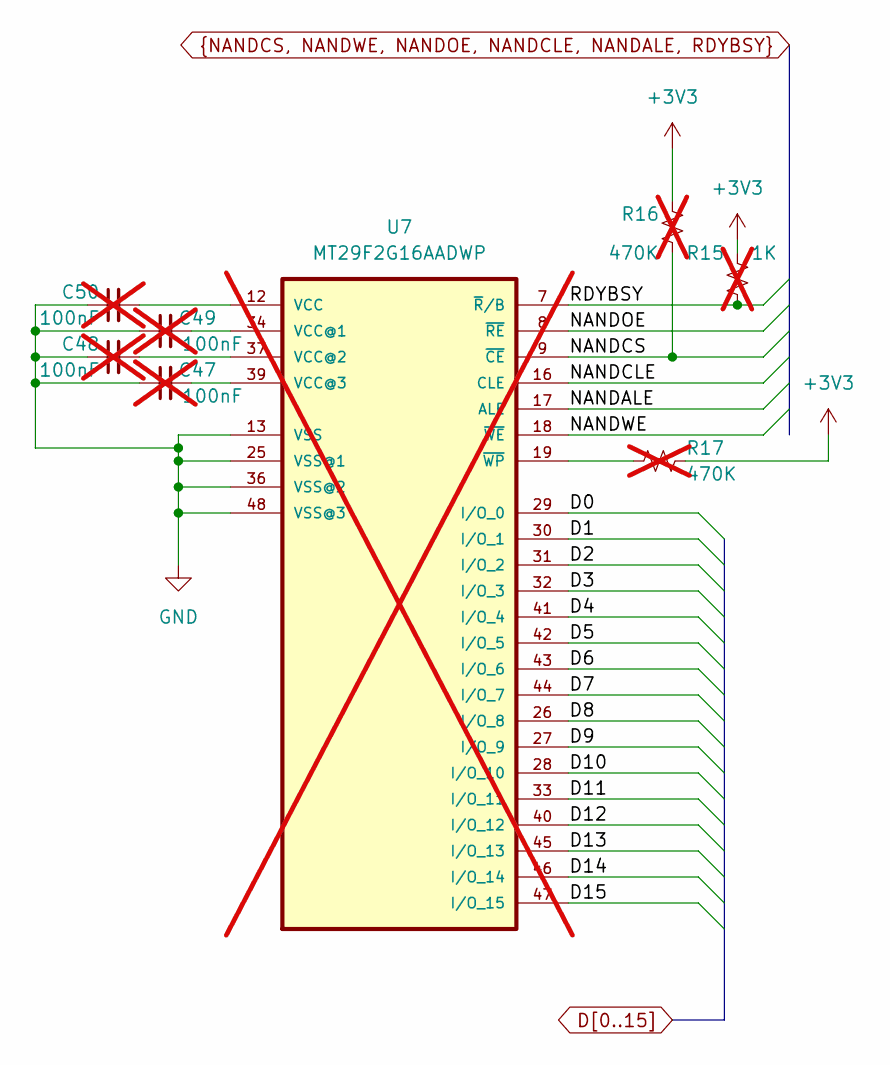
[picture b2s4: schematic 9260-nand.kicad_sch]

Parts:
C47, C48, C49, C50: 100nF; C_0805_2012Metric; not fitted
R15: 1K; R_0805_2012Metric; not fitted
R16, R17: 470K; R_0805_2012Metric; not fitted
U7: MT29F2G16AADWP; TSOP-48; not fitted

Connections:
unnamed: C47.1, C48.1, C49.1, C50.1, U7.13 (VSS), U7.25 (VSS@1), U7.36 (VSS@2), U7.48 (VSS@3)
unnamed: C47.2, U7.39 (VCC@3)
unnamed: C48.2, U7.37 (VCC@2)
unnamed: C49.2, U7.34 (VCC@1)
unnamed: C50.2, U7.12 (VCC)
unnamed: R15.1, R16.1, R17.1
unnamed: R15.2, U7.7 (~R/B)
unnamed: R16.2, U7.9 (~CE)
unnamed: R17.2, U7.19 (~WP)

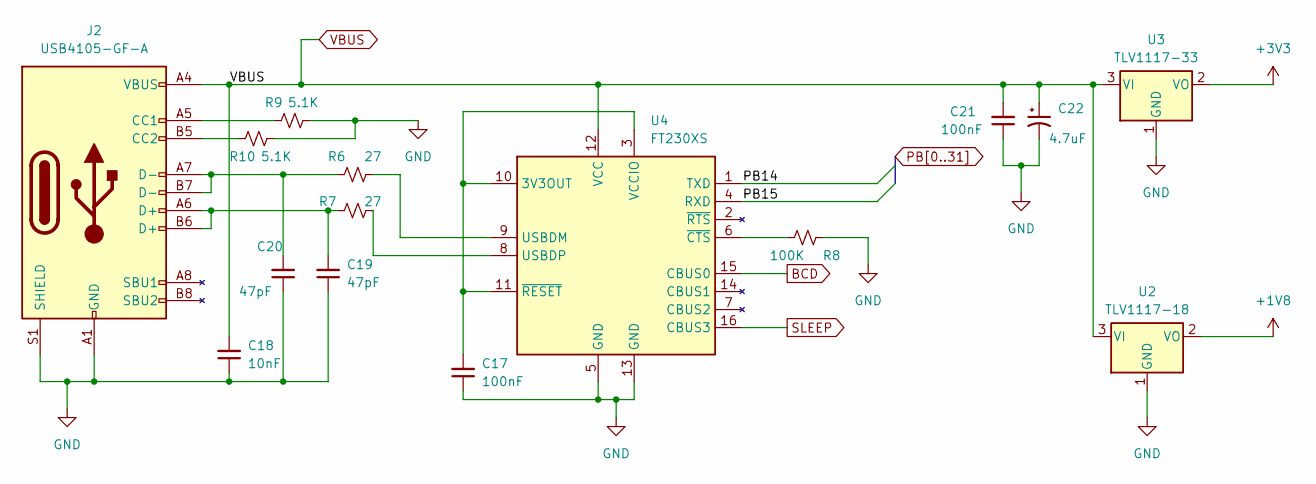
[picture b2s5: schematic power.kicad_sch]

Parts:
C17, C21: 100nF; C_0805_2012Metric
C18: 10nF; C_0805_2012Metric
C19, C20: 47pF; C_0805_2012Metric
C22: 4.7uF; C_0805_2012Metric
J2: USB4105-GF-A; USB_C_Receptacle_GCT_USB4105-xx-A_16P_TopMnt_Horizontal
R6, R7: 27; R_0805_2012Metric
R8: 100K; R_0805_2012Metric
R9, R10: 5.1K; R_0805_2012Metric
U2: TLV1117-18; SOT-223-3_TabPin2
U3: TLV1117-33; SOT-223-3_TabPin2
U4: FT230XS; SSOP-16_3.9x4.9mm_P0.635mm

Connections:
1V8: U2.2 (VO); also elsewhere on the board
3V3: U3.2 (VO); also elsewhere on the board
BCD: U4.15 (CBUS0)
GND: C17.1, C18.1, C19.1, C20.1, C21.1, C22.2, J2.A1 (GND), J2.A12 (GND), J2.B1 (GND), J2.B12 (GND), J2.S1 (SHIELD), R8.2, R9.2, R10.2, U2.1 (GND), U3.1 (GND), U4.5 (GND), U4.13 (GND); also elsewhere on the board
unnamed: C19.2, J2.A6 (D+), J2.B6 (D+), R7.1
unnamed: C20.2, J2.A7 (D-), J2.B7 (D-), R6.1
unnamed: J2.A5 (CC1), R9.1
unnamed: J2.B5 (CC2), R10.1
unnamed: C17.2, U4.3 (VCCIO), U4.10 (3V3OUT), U4.11 (~RESET)
unnamed: R6.2, U4.9 (USBDM)
unnamed: R7.2, U4.8 (USBDP)
unnamed: R8.1, U4.6 (~CTS)
PB14: U4.1 (TXD); also elsewhere on the board
PB15: U4.4 (RXD); also elsewhere on the board
SLEEP: U4.16 (CBUS3)
VBUS: C18.2, C21.2, C22.1, J2.A4 (VBUS), J2.A9 (VBUS), J2.B4 (VBUS), J2.B9 (VBUS), U2.3 (VI), U3.3 (VI), U4.12 (VCC); also elsewhere on the board

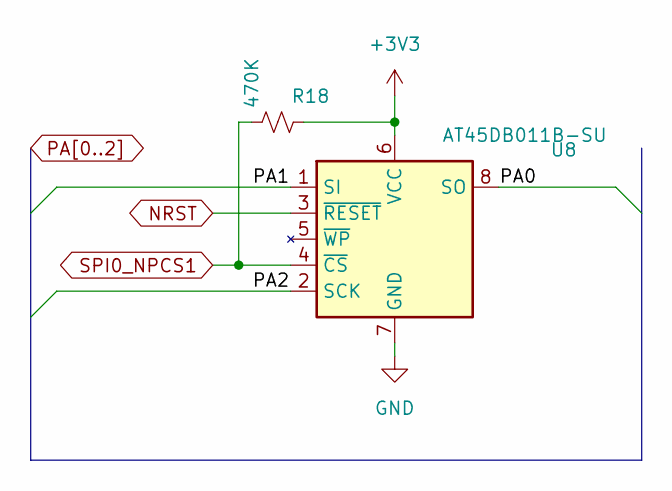
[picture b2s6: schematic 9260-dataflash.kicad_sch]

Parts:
R18: 470K; R_0805_2012Metric
U8: AT45DB011B-SU; SOIC-8_5.275x5.275mm_P1.27mm

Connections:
3V3: R18.1, U8.6 (VCC); also elsewhere on the board
GND: U8.7 (GND); also elsewhere on the board
NRST: U8.3 (~RESET); also elsewhere on the board
PA0: U8.8 (SO); also elsewhere on the board
PA1: U8.1 (SI); also elsewhere on the board
PA2: U8.2 (SCK); also elsewhere on the board
SPI0_NPCS1: R18.2, U8.4 (~CS); also elsewhere on the board

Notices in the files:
IMX6QP/IMX6QP.kicad_pcb:
LICENSE: LGPL
